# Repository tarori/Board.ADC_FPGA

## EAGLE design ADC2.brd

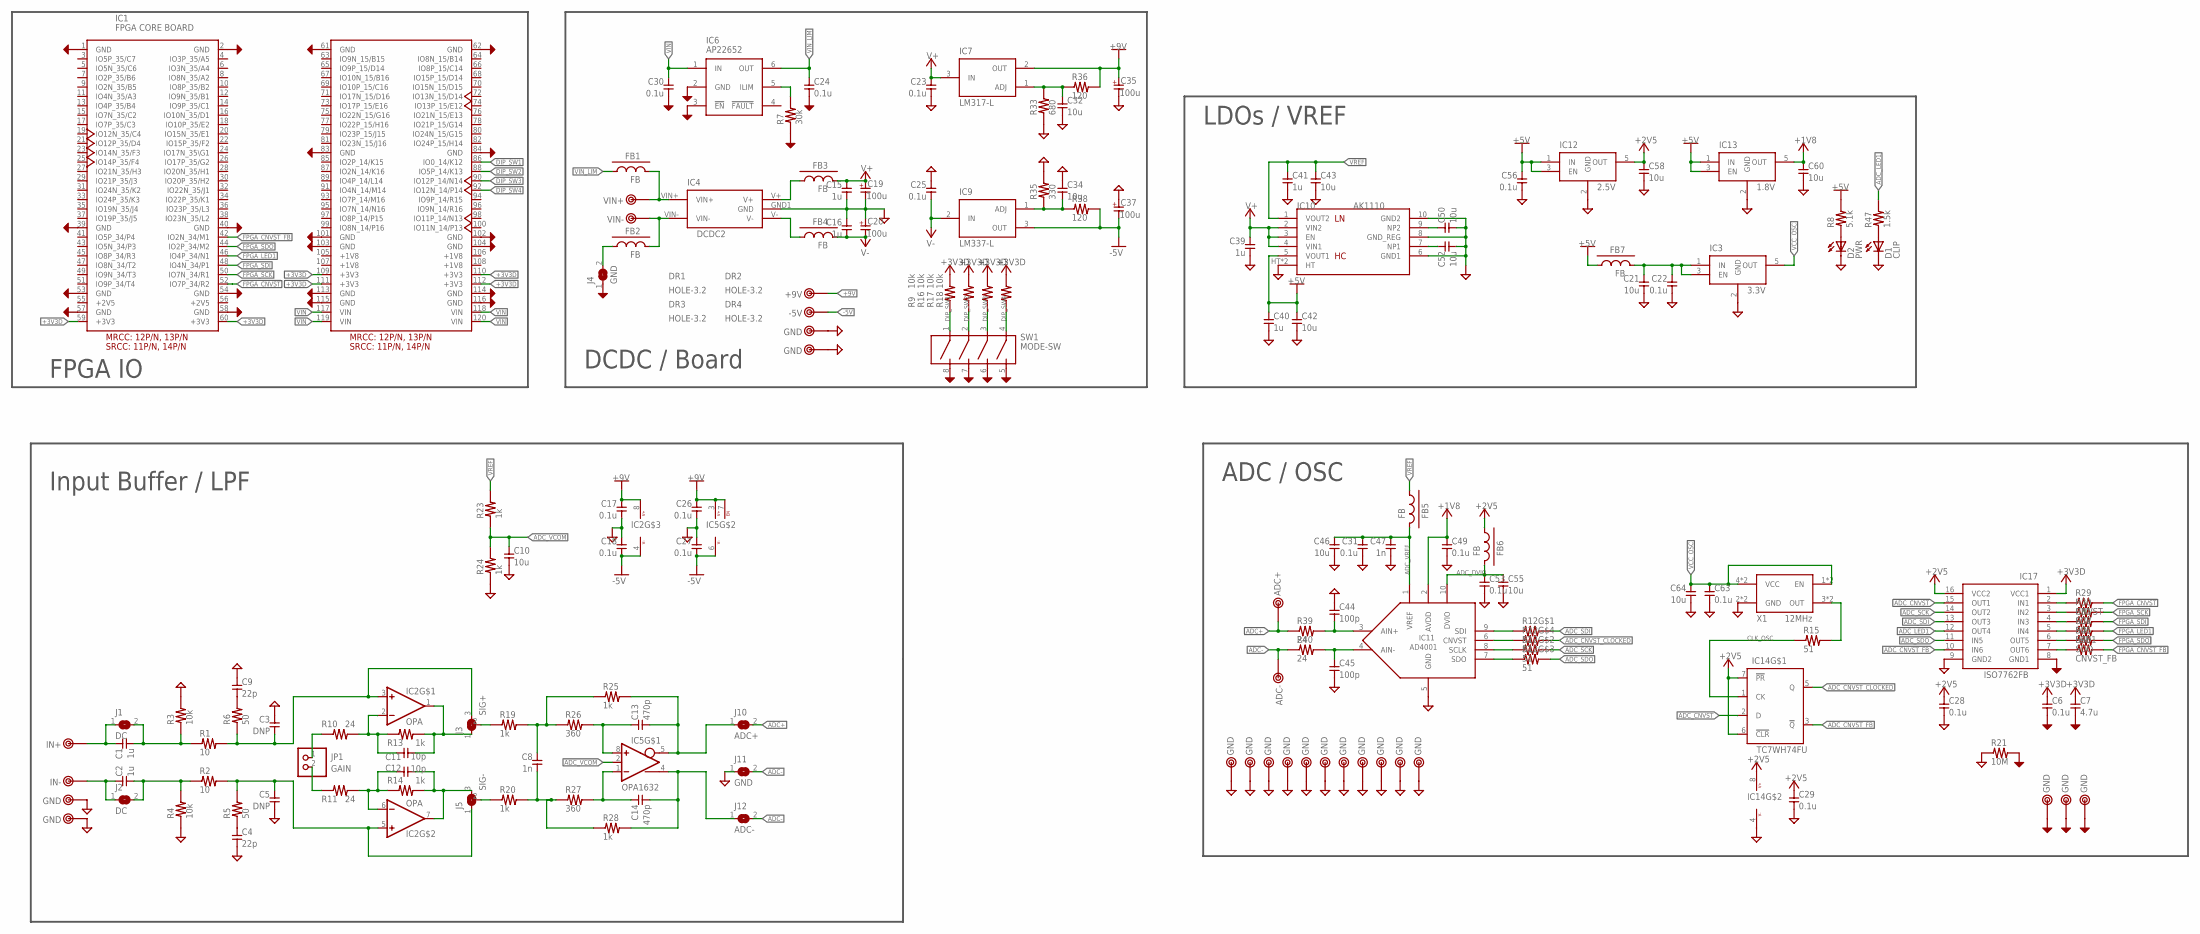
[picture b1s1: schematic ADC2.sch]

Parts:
C1, C2: 1u; 3225
C3, C5: DNP; 1608C
C4, C9: 22p; 1608C
C6, C17, C18, C22, C23, C24, C25, C26, C27, C28, C29, C30, C31, C49, C53, C56, C63: 0.1u; 1608C
C7: 4.7u; 1608C
C8: 1n; 1608C
C10, C21, C42, C46, C50, C52, C55, C58, C60, C64: 10u; 2012
C11, C12: 10p; 1608C
C13, C14: 470p; 1608C
C15, C16, C39, C40, C41: 1u; 1608C
C19, C20: 100u; E2,5-8
C32, C34, C43: 10u; 3216
C35, C37: 100u; E2.5-6.5
C44, C45: 100p; 1608C
C47: 1n; 1005
D1: CLIP; D1608
D2: PWR; D1608
DR1, DR2, DR3, DR4: HOLE-3.2; HOLE_3.2
FB1, FB2, FB3, FB4: FB; 2012-J
FB5, FB6, FB7: FB; 1608-FB
IC1: FPGA CORE BOARD; FPGA_CORE_BOARD
IC2: OPA; SOP8-3
IC3: 3.3V; SOT23-5
IC4: DCDC2
IC5: OPA1632; SOP8-3
IC6: AP22652; SOT23-6
IC7: LM317-L; TO-92
IC9: LM337-L; TO-92
IC10: AK1110; PLP10
IC11: AD4001; MSOP10
IC12: 2.5V; SOT23-5
IC13: 1.8V; SOT23-5
IC14: TC7WH74FU; SSOP8-P-0.65
IC17: ISO7762FB; TSSOP16
J1, J2: DC; 1608-J
J3: SIG+; 1608-3-J
J4: GND; 2012-J
J5: SIG-; 1608-3-J
J10: ADC+; 1608-J
J11: GND; 1608-J
J12: ADC-; 1608-J
JP1: GAIN; 1X02
R1, R2: 10; 2012-R
R3, R4, R9, R16, R17, R18: 10k; 1608
R5, R6: 50; 1608
R7: 30k; 1608
R8: 5.1k; 1608
R10, R11, R39, R40: 24; 1608-3
R12: 51; EXB28V
R13, R14, R23, R24: 1k; 1608
R15: 51; 1608-3
R19, R20, R25, R28: 1k; 1608-3
R21: 10M; 0204/7
R26, R27: 360; 1608-3
R29: CNVST; 1608-3
R30: SCK; 1608-3
R31: SDI; 1608-3
R32: LED1; 1608-3
R33: 680; 1608
R35: 330; 1608
R36, R38: 120; 1608
R45: SDO; 1608-3
R46: CNVST_FB; 1608-3
R47: 1.5k; 1608
SW1: MODE-SW; DIPSW-4
TP1, TP3: GND; TESTPIN-MID
TP2: IN+; TESTPIN-MID
TP4, TP5, TP7, TP8, TP9, TP10, TP11, TP12, TP15, TP16, TP17, TP18, TP19, TP22, TP23, TP24: GND; TESTPIN
TP6: IN-; TESTPIN-MID
TP13: ADC+; TESTPIN
TP14: ADC-; TESTPIN
TP20: -5V; TESTPIN
TP21: +9V; TESTPIN
TP30: VIN+; TESTPIN
TP31: VIN-; TESTPIN
X1: 12MHz; KC7050

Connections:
+1V8: C49.1, C60.1, IC11.2 (AVDD), IC13.5 (OUT)
+2V5: C28.1, C29.1, C58.1, FB6.1, IC12.5 (OUT), IC14.6 (!CLR), IC14.7 (!PR), IC14.8 (V+), IC17.16 (VCC2)
+3V3D: C6.1, C7.1, IC1.59 (+3V3), IC1.60 (+3V3), IC1.109 (+3V3), IC1.110 (+3V3), IC1.111 (+3V3), IC1.112 (+3V3), IC17.1 (VCC1), R9.2, R16.2, R17.2, R18.2
+5V: C40.1, C42.1, C56.1, FB7.1, IC10.5 (VOUT1), IC12.1 (IN), IC12.3 (EN), IC13.1 (IN), IC13.3 (EN), R8.2
+9V: C17.1, C26.1, C35.+ (1), IC2.8 (V+), IC5.3 (V+), IC5.7 (EN), IC7.2 (OUT), R36.2, TP21.1
-5V: C18.2, C27.2, C37.- (2), IC2.4 (V-), IC5.6 (V-), IC9.3 (OUT), R38.2, TP20.1
ADC+: J10.2, R39.1, TP13.1
ADC+_LPF: C44.2, IC11.3 (AIN+), R39.2
ADC-: J11.2, J12.2, R40.1, TP14.1
ADC-_LPF: C45.1, IC11.4 (AIN-), R40.2
ADC_CNVST: IC14.2 (D), IC17.15 (OUT1)
ADC_CNVST_CLOCKED: IC14.5 (Q), R12.5 (2)
ADC_CNVST_FB: IC14.3 (!Q), IC17.10 (IN6)
ADC_DVIO: C53.1, C55.1, FB6.2, IC11.10 (DVIO)
ADC_LED1: IC17.12 (OUT4), R47.2
ADC_SCK: IC17.14 (OUT2), R12.7 (2)
ADC_SDI: IC17.13 (OUT3), R12.8 (2)
ADC_SDO: IC17.11 (IN5), R12.6 (2)
ADC_VCOM: C10.1, IC5.2 (CM), R23.1, R24.2
ADC_VREF: C31.1, C46.1, C47.1, FB5.2, IC11.1 (VREF)
CLK_OSC: IC14.1 (CK), R15.1
DGND: C6.2, C7.2, C24.2, C30.2, IC1.1 (GND), IC1.2 (GND), IC1.39 (GND), IC1.40 (GND), IC1.53 (GND), IC1.54 (GND), IC1.57 (GND), IC1.58 (GND), IC1.61 (GND), IC1.62 (GND), IC1.83 (GND), IC1.84 (GND), IC1.101 (GND), IC1.102 (GND), IC1.103 (GND), IC1.104 (GND), IC1.113 (GND), IC1.114 (GND), IC1.115 (GND), IC1.116 (GND), IC6.2 (GND), IC6.3 (!EN), IC17.8 (GND1), J4.1, R7.1, R21.2, SW1.5 (B4), SW1.6 (B3), SW1.7 (B2), SW1.8 (B1), TP22.1, TP23.1, TP24.1
DIP_SW1: IC1.86 (IO0_14/K12), R9.1, SW1.1 (A1)
DIP_SW2: IC1.88 (IO5P_14/K13), R16.1, SW1.2 (A2)
DIP_SW3: IC1.90 (IO12P_14/N14), R17.1, SW1.3 (A3)
DIP_SW4: IC1.92 (IO12N_14/P14), R18.1, SW1.4 (A4)
FPGA_CNVST: IC1.52 (IO7P_34/R2), R29.2
FPGA_CNVST_FB: IC1.42 (IO2N_34/M1), R46.2
FPGA_LED1: IC1.46 (IO4P_34/N1), R32.2
FPGA_SCK: IC1.50 (IO7N_34/R1), R30.2
FPGA_SDI: IC1.48 (IO4N_34/P1), R31.2
FPGA_SDO: IC1.44 (IO2P_34/M2), R45.2
GND: C3.1, C4.2, C5.2, C9.1, C10.2, C15.2, C16.1, C17.2, C18.1, C19.- (2), C20.+ (1), C21.2, C22.2, C23.2, C25.1, C26.2, C27.1, C28.2, C29.2, C31.2, C32.2, C34.1, C35.- (2), C37.+ (1), C39.2, C40.2, C41.2, C42.2, C43.2, C44.1, C45.2, C46.2, C47.2, C49.2, C50.2, C52.2, C53.2, C55.2, C56.2, C58.2, C60.2, C63.2, C64.2, D1.K, D2.K, IC3.2 (GND), IC4.GND1 (GND), IC10.6 (GND1), IC10.8 (GND_REG), IC10.10 (GND2), IC10.HT, IC10.HT2 (HT), IC11.5 (GND), IC12.2 (GND), IC13.2 (GND), IC14.4 (V-), IC17.9 (GND2), J11.1, R3.2, R4.1, R21.1, R24.1, R33.1, R35.2, TP1.1, TP3.1, TP4.1, TP5.1, TP7.1, TP8.1, TP9.1, TP10.1, TP11.1, TP12.1, TP15.1, TP16.1, TP17.1, TP18.1, TP19.1, X1.2 (GND), X1.2-2 (GND)
unnamed: J5.2, R20.1
unnamed: IC17.7 (OUT6), R46.1
unnamed: C11.1, IC2.2 (-IN), R10.2, R13.1
unnamed: C11.2, IC2.1 (OUT), J3.1, R13.2
unnamed: IC17.6 (OUT5), R45.1
unnamed: J3.2, R19.1
unnamed: C52.1, IC10.7 (NP1)
unnamed: C50.1, IC10.9 (NP2)
unnamed: C4.1, R5.1
unnamed: C12.1, IC2.6 (-IN), R11.2, R14.1
unnamed: IC17.5 (IN4), R32.1
unnamed: C9.2, R6.2
unnamed: IC17.4 (IN3), R31.1
unnamed: C3.2, IC2.3 (+IN), J3.3, R1.2, R6.1
unnamed: C21.1, C22.1, FB7.2, IC3.1 (IN), IC3.3 (EN)
unnamed: C8.1, R19.2, R25.1, R26.1
unnamed: IC17.3 (IN2), R30.1
unnamed: IC17.2 (IN1), R29.1
unnamed: R15.2, X1.3 (OUT), X1.3-2 (OUT)
unnamed: C12.2, IC2.7 (OUT), J5.3, R14.2
unnamed: C8.2, R20.2, R27.1, R28.1
unnamed: C5.1, IC2.5 (+IN), J5.1, R2.2, R5.2
unnamed: IC6.5 (ILIM), R7.2
unnamed: IC11.7 (SDO), R12.3 (1)
unnamed: D2.A, R8.1
unnamed: C13.1, IC5.8 (+IN), R26.2
unnamed: IC11.8 (SCLK), R12.2 (1)
unnamed: IC11.6 (CNVST), R12.4 (1)
unnamed: IC11.9 (SDI), R12.1
unnamed: C13.2, IC5.5 (-OUT), J10.1, R25.2
unnamed: C14.2, IC5.4 (+OUT), J12.1, R28.2
unnamed: C14.1, IC5.1 (-IN), R27.2
unnamed: C1.1, J1.1, TP2.1
unnamed: C2.1, J2.1, TP6.1
unnamed: C1.2, J1.2, R1.1, R3.1
unnamed: C2.2, J2.2, R2.1, R4.2
unnamed: JP1.1, R10.1
unnamed: JP1.2, R11.1
unnamed: C32.1, IC7.1 (ADJ), R33.2, R36.1
unnamed: C34.2, IC9.1 (ADJ), R35.1, R38.1
unnamed: FB2.1, J4.2
unnamed: D1.A, R47.1
unnamed: FB3.1, IC4.V+
unnamed: FB4.1, IC4.V-
unnamed: FB1.2, IC4.VIN+, TP30.1
unnamed: FB2.2, IC4.VIN-, TP31.1
V+: C15.1, C19.+ (1), C23.1, C39.1, FB3.2, IC7.3 (IN), IC10.2 (VIN2), IC10.3 (EN), IC10.4 (VIN1)
V-: C16.2, C20.- (2), C25.2, FB4.2, IC9.2 (IN)
VCC_OSC: C63.1, C64.1, IC3.5 (OUT), X1.1 (EN), X1.1-2 (EN), X1.4 (VCC), X1.4-2 (VCC)
VIN: C30.1, IC1.117 (VIN), IC1.118 (VIN), IC1.119 (VIN), IC1.120 (VIN), IC6.1 (IN)
VIN_LIM: C24.1, FB1.1, IC6.6 (OUT)
VREF: C41.1, C43.1, FB5.1, IC10.1 (VOUT2), R23.2

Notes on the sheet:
Input Buffer / LPF
LDOs / VREF
ADC / OSC
DCDC / Board
FPGA IO

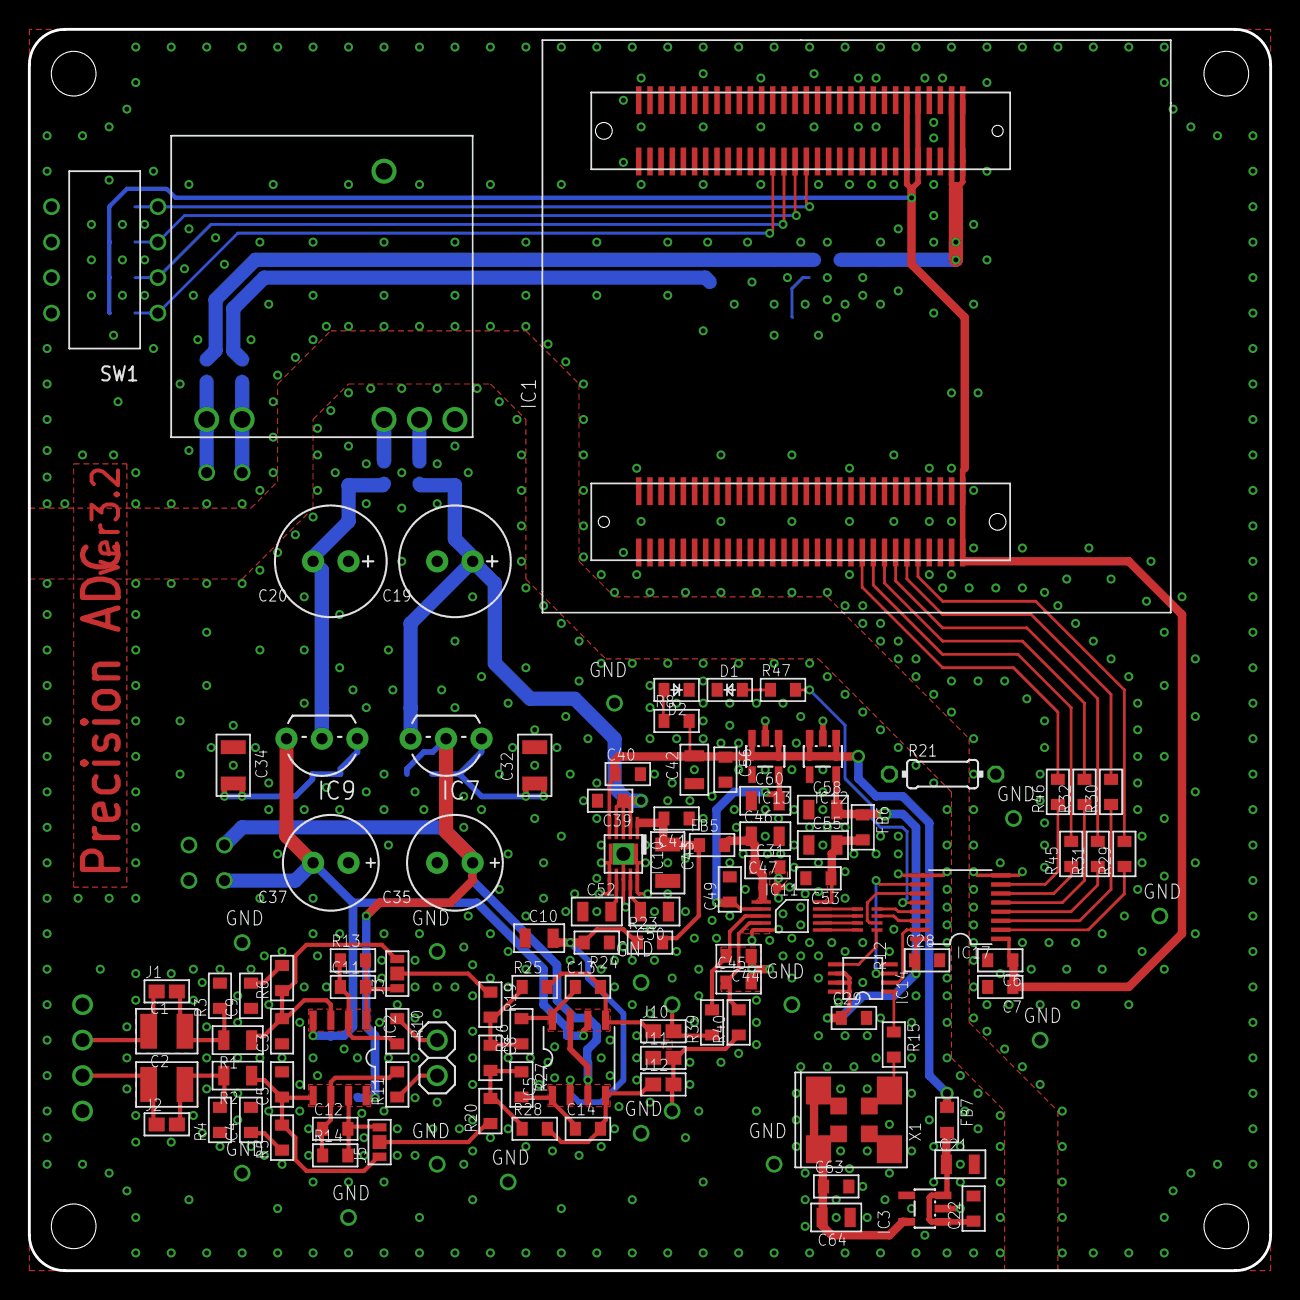
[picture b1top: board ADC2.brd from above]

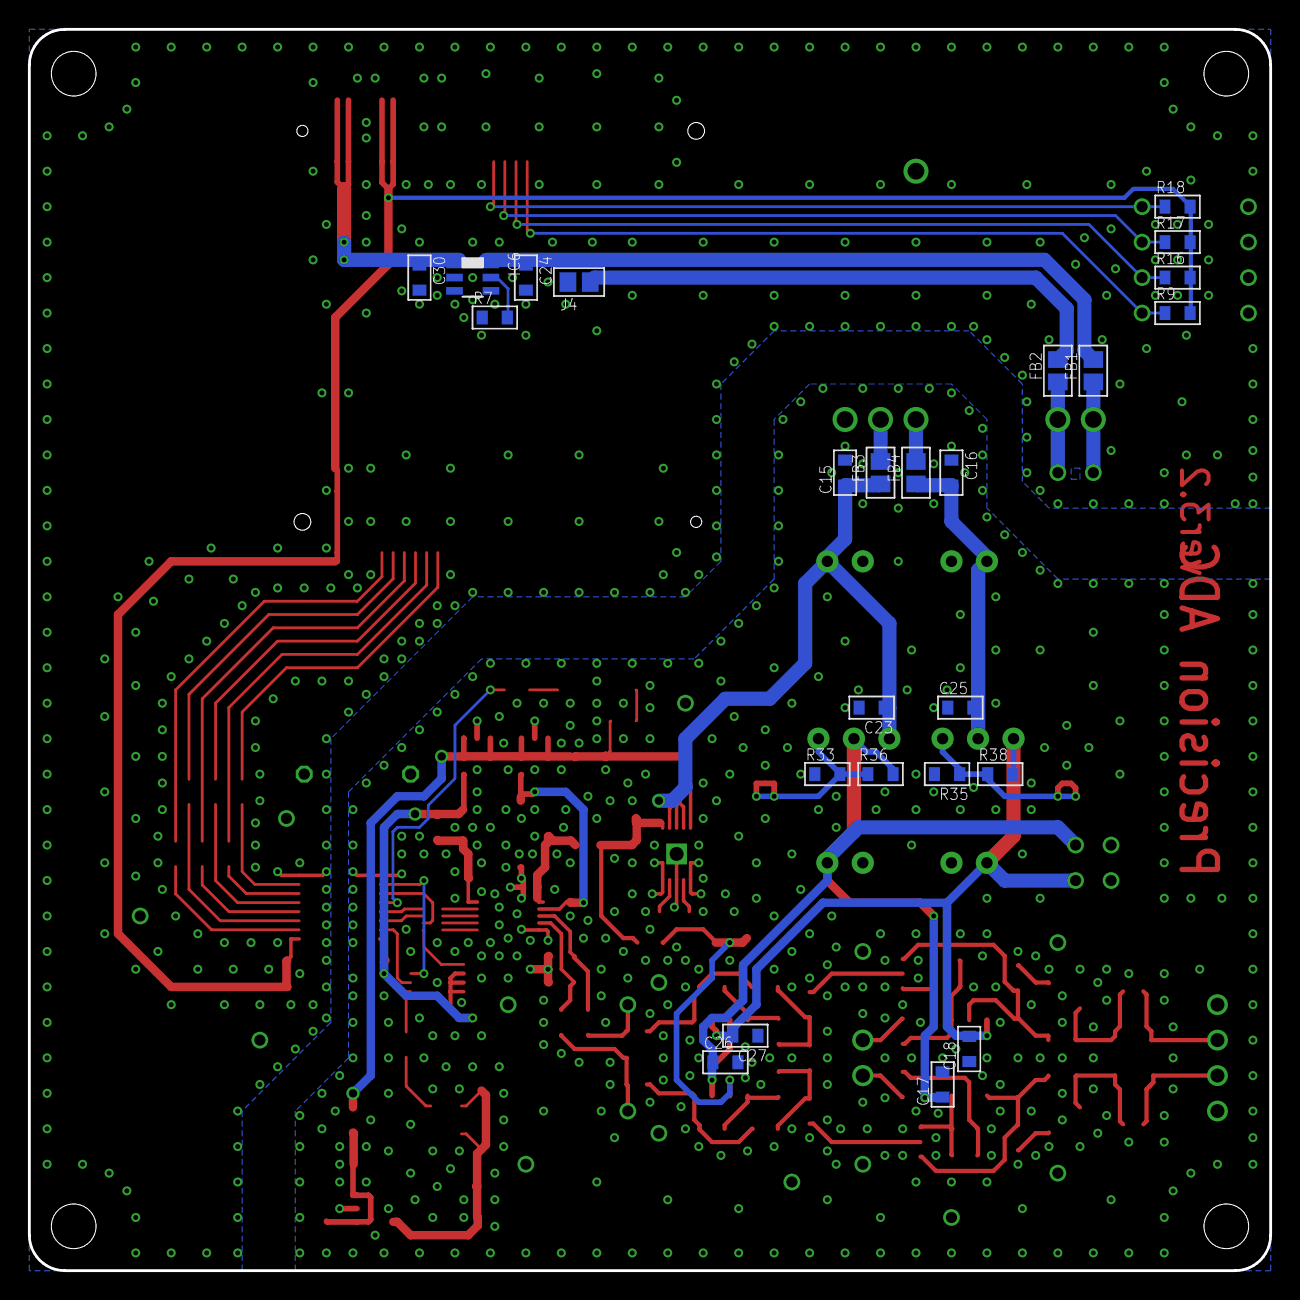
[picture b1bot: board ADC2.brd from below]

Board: 4 copper layers, 88.9 x 88.9 mm, 158 parts (25 on the bottom side), 85 nets.

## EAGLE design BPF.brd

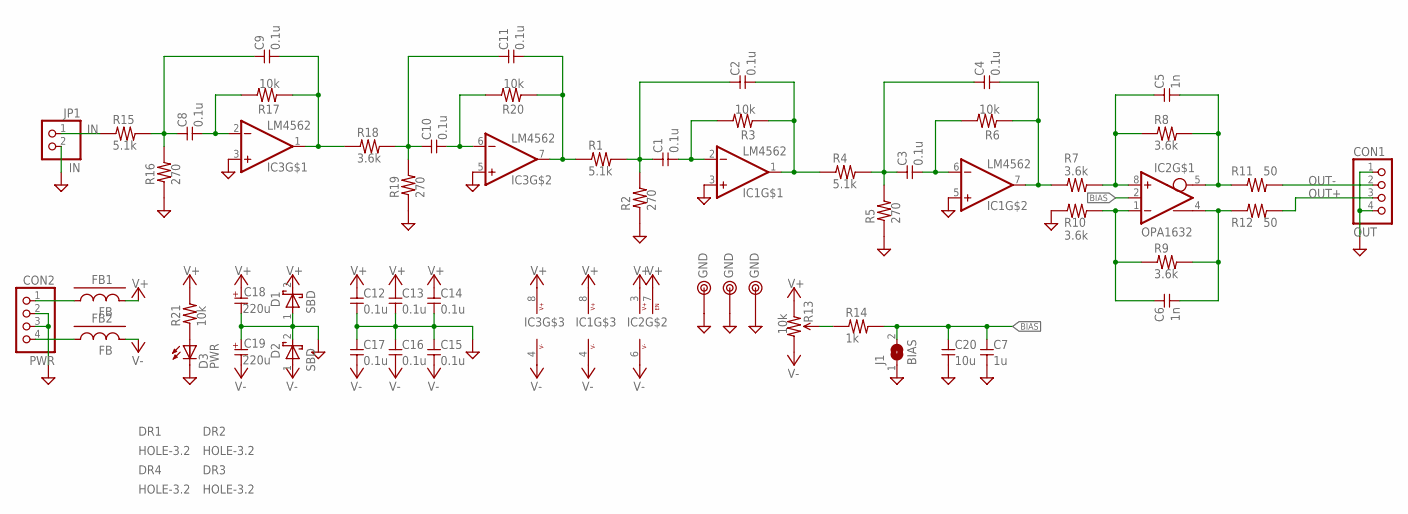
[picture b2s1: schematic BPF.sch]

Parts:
C1, C2, C3, C4, C8, C9, C10, C11: 0.1u; C050W
C5, C6: 1n; 2012
C7: 1u; 1608C
C12, C13, C14, C15, C16, C17: 0.1u; 1608C
C18, C19: 220u; E2,5-8
C20: 10u; 3216
CON1: OUT; 1X04
CON2: PWR; 1X04
D1, D2: SBD; SOD123
D3: PWR; D1608
DR1, DR2, DR3, DR4: HOLE-3.2; HOLE_3.2
FB1, FB2: FB; 2012-R
IC1, IC3: LM4562; SOP8
IC2: OPA1632; SOP8
J1: BIAS; 1608-J
JP1: IN; 1X02
R1, R4, R15: 5.1k; 2012
R2, R5, R16, R19: 270; 2012
R3, R6, R17, R20: 10k; 2012
R7, R8, R9, R10, R18: 3.6k; 2012
R11, R12: 50; 1608
R13: 10k; 3296W
R14: 1k; 1608
R21: 10k; 1608
TP1, TP2, TP3: GND; TESTPIN

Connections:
BIAS: C7.1, C20.1, IC2.2 (CM), J1.2, R14.2
GND: C7.2, C12.2, C13.2, C14.2, C15.1, C16.1, C17.1, C18.- (2), C19.+ (1), C20.2, CON1.1, CON1.4, CON2.2, CON2.3, D1.1 (A), D2.2 (K), D3.K, IC1.3 (+IN), IC1.5 (+IN), IC3.3 (+IN), IC3.5 (+IN), J1.1, JP1.2, R2.1, R5.1, R10.1, R16.1, R19.1, TP1.1, TP2.1, TP3.1
IN: JP1.1, R15.1
unnamed: C1.1, C1.3 (1), C2.1, C2.3 (1), R1.2, R2.2
unnamed: C1.2, C1.4 (2), IC1.2 (-IN), R3.2
unnamed: C2.2, C2.4 (2), IC1.1 (OUT), R3.1, R4.1
unnamed: C4.2, C4.4 (2), IC1.7 (OUT), R6.1, R7.1
unnamed: C3.1, C3.3 (1), C4.1, C4.3 (1), R4.2, R5.2
unnamed: C3.2, C3.4 (2), IC1.6 (-IN), R6.2
unnamed: CON2.1, FB1.1
unnamed: C5.1, IC2.8 (+IN), R7.2, R8.1
unnamed: C6.1, IC2.1 (-IN), R9.1, R10.2
unnamed: C8.1, C8.3 (1), C9.1, C9.3 (1), R15.2, R16.2
unnamed: C5.2, IC2.5 (-OUT), R8.2, R11.1
unnamed: C6.2, IC2.4 (+OUT), R9.2, R12.1
unnamed: C8.2, C8.4 (2), IC3.2 (-IN), R17.2
unnamed: R13.2, R14.1
unnamed: C9.2, C9.4 (2), IC3.1 (OUT), R17.1, R18.1
unnamed: C11.2, C11.4 (2), IC3.7 (OUT), R1.1, R20.1
unnamed: C10.1, C10.3 (1), C11.1, C11.3 (1), R18.2, R19.2
unnamed: C10.2, C10.4 (2), IC3.6 (-IN), R20.2
unnamed: CON2.4, FB2.1
unnamed: D3.A, R21.1
OUT+: CON1.3, R12.2
OUT-: CON1.2, R11.2
V+: C12.1, C13.1, C14.1, C18.+ (1), D1.2 (K), FB1.2, IC1.8 (V+), IC2.3 (V+), IC2.7 (EN), IC3.8 (V+), R13.1, R21.2
V-: C15.2, C16.2, C17.2, C19.- (2), D2.1 (A), FB2.2, IC1.4 (V-), IC2.6 (V-), IC3.4 (V-), R13.3

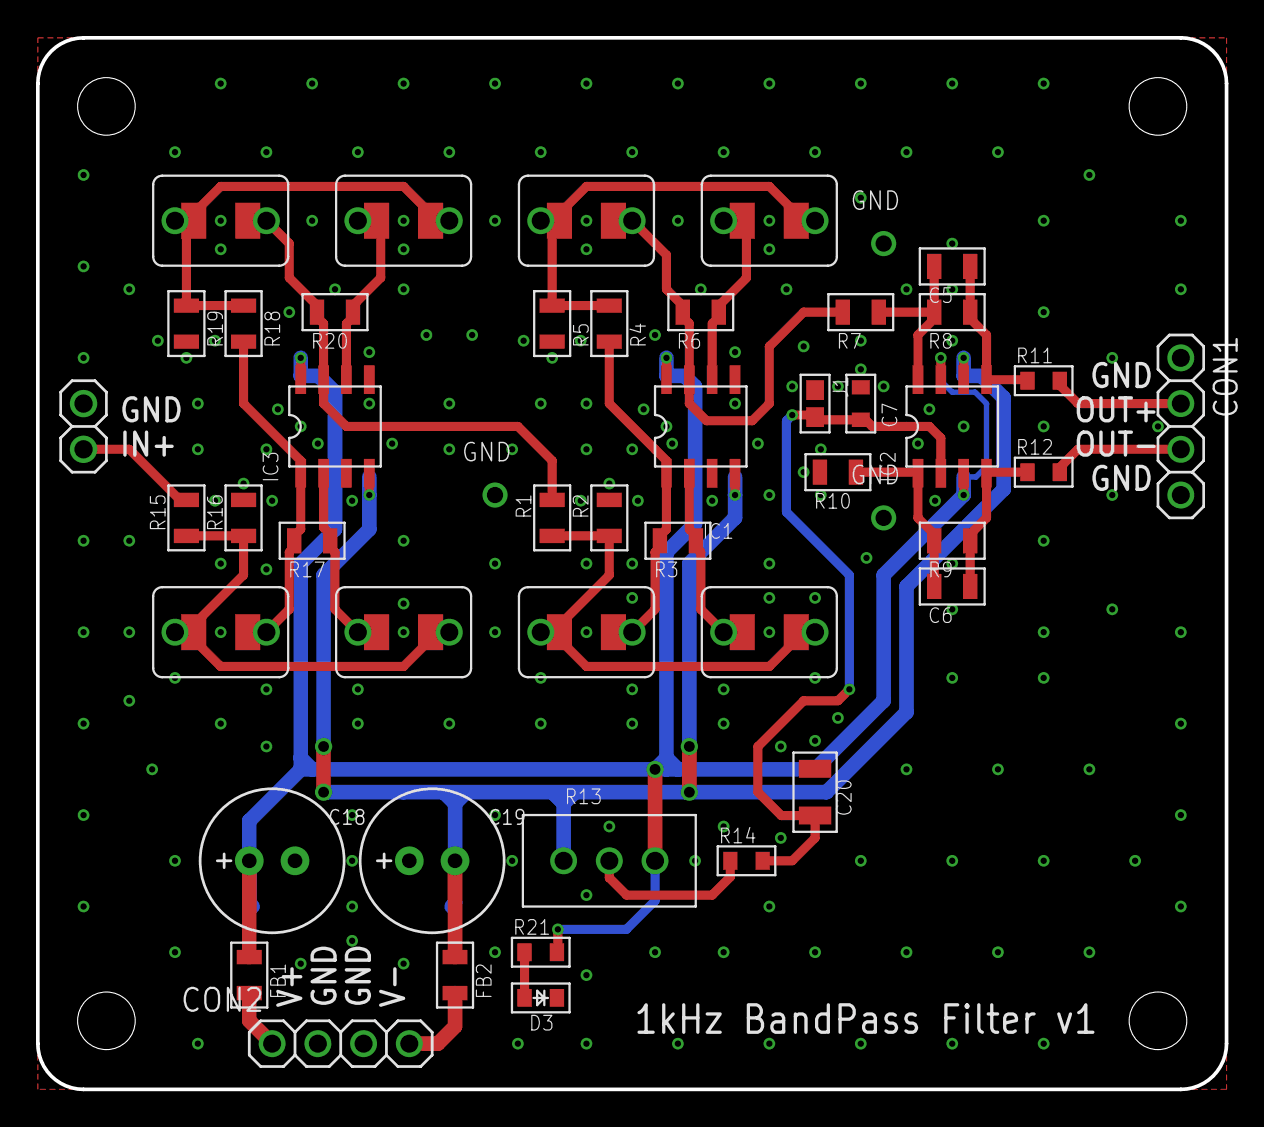
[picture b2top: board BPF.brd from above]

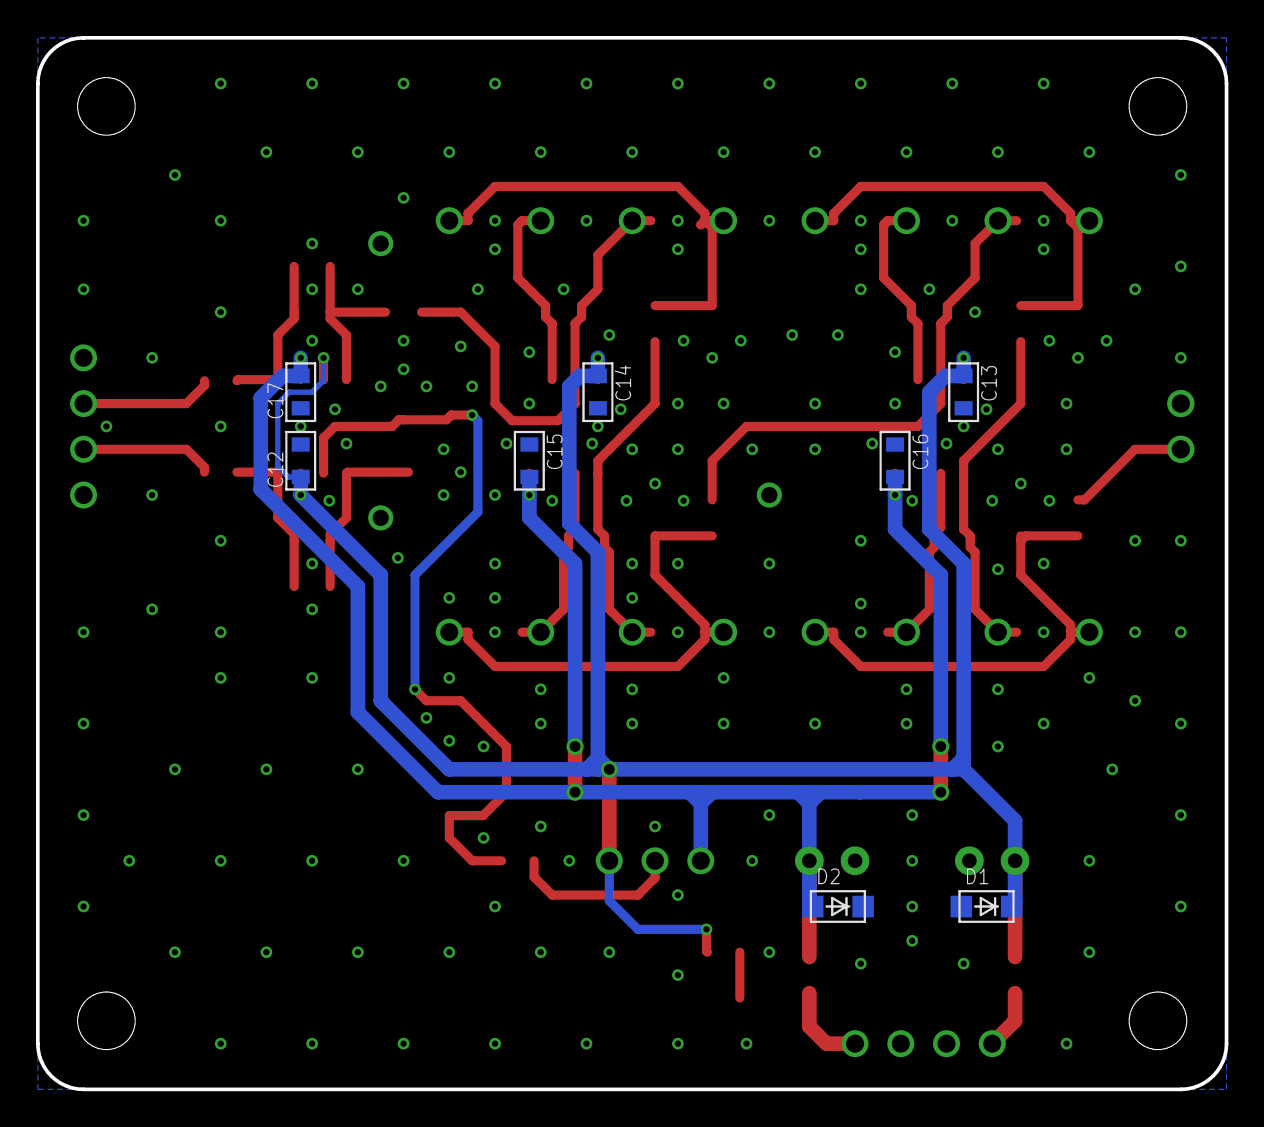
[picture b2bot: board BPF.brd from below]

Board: 4 copper layers, 66.0 x 58.4 mm, 60 parts (8 on the bottom side), 27 nets.

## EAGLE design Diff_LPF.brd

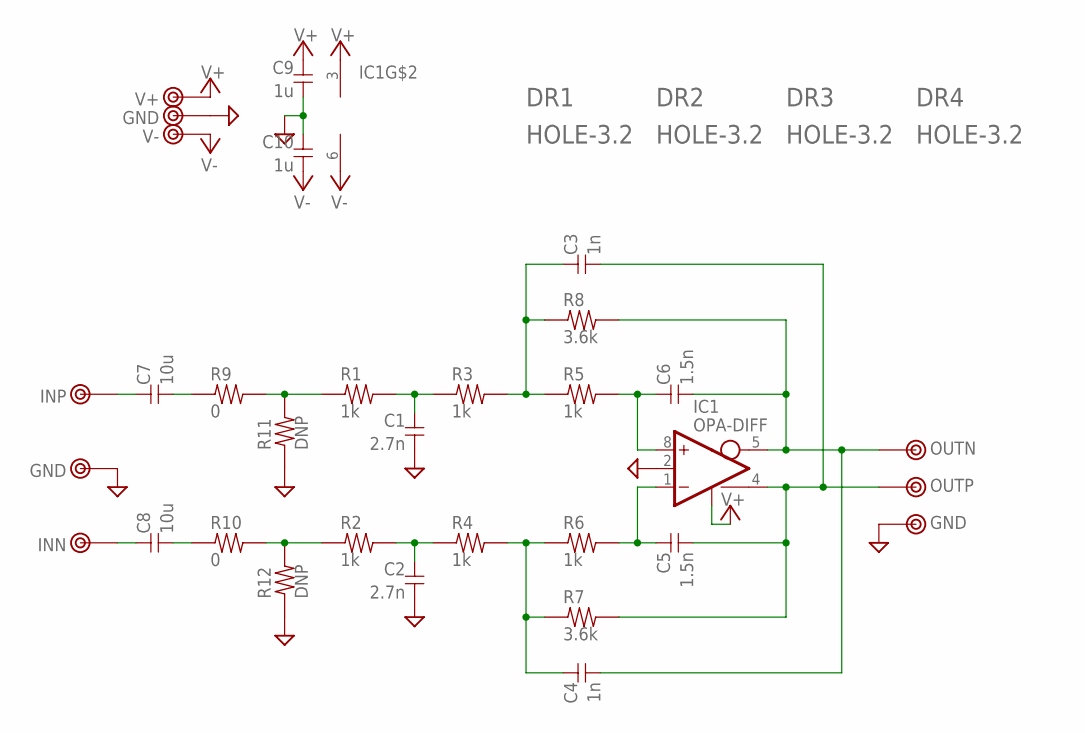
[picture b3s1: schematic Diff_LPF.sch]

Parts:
C1, C2: 2.7n; 1608C
C3, C4: 1n; 1608C
C5, C6: 1.5n; 1608C
C7, C8: 10u; C050W
C9, C10: 1u; 1608C
DR1, DR2, DR3, DR4: HOLE-3.2; HOLE_3.2
IC1: OPA-DIFF; SOP8
R1, R2, R3, R4, R5, R6: 1k; 1608
R7, R8: 3.6k; 1608
R9, R10: 0; 1608
R11, R12: DNP; 1608
TP1: INP; TESTPIN-MID
TP2: INN; TESTPIN-MID
TP3: OUTN; TESTPIN-MID
TP4: OUTP; TESTPIN-MID
TP5: V+; TESTPIN-MID
TP6, TP8, TP9: GND; TESTPIN-MID
TP7: V-; TESTPIN-MID

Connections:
GND: C1.2, C2.2, C9.2, C10.1, IC1.2 (CM), R11.1, R12.1, TP6.1, TP8.1, TP9.1
unnamed: R1.1, R9.2, R11.2
unnamed: R2.1, R10.2, R12.2
unnamed: C1.1, R1.2, R3.1
unnamed: C2.1, R2.2, R4.1
unnamed: C6.1, IC1.8 (+IN), R5.2
unnamed: C4.2, C6.2, IC1.5 (-OUT), R8.2, TP3.1
unnamed: C3.2, C5.2, IC1.4 (+OUT), R7.2, TP4.1
unnamed: C5.1, IC1.1 (-IN), R6.2
unnamed: C4.1, R4.2, R6.1, R7.1
unnamed: C3.1, R3.2, R5.1, R8.1
unnamed: C7.2, C7.4 (2), R9.1
unnamed: C8.2, C8.4 (2), R10.1
unnamed: C7.1, C7.3 (1), TP1.1
unnamed: C8.1, C8.3 (1), TP2.1
V+: C9.1, IC1.3 (V+), IC1.7 (EN), TP5.1
V-: C10.2, IC1.6 (V-), TP7.1

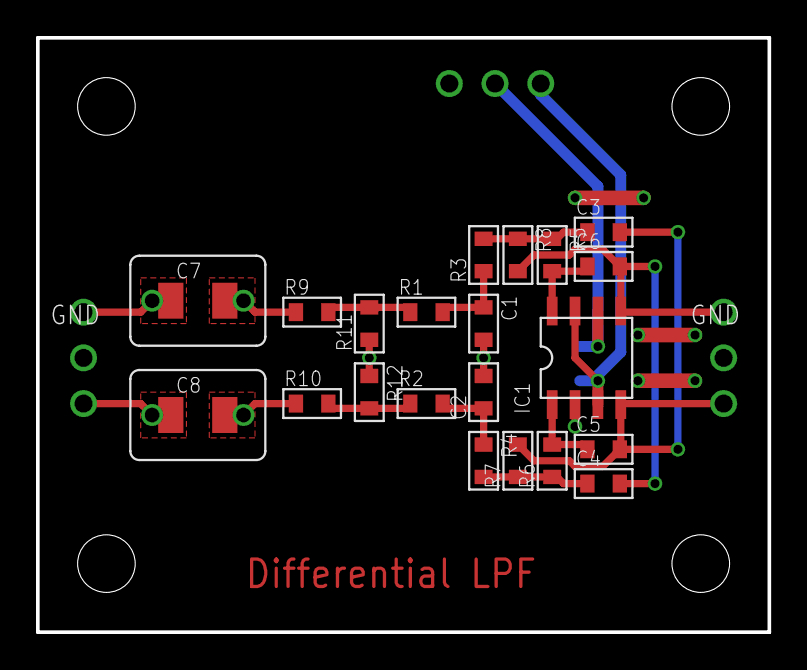
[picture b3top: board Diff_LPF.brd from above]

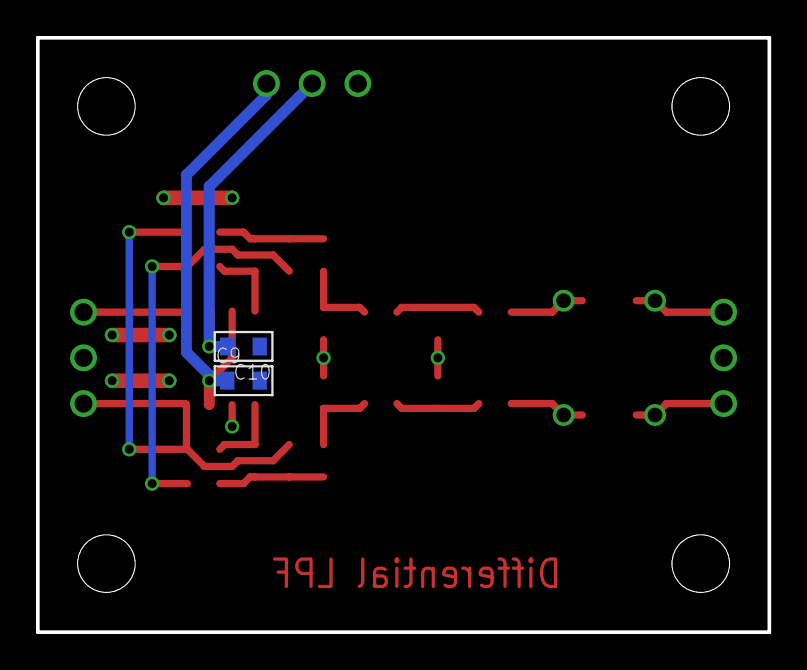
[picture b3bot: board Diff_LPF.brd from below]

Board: 2 copper layers, 40.6 x 33.0 mm, 36 parts (2 on the bottom side), 17 nets.
